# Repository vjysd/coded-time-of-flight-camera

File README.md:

# Coded Time of Flight Imaging System

## Motivation
Depth accuracy has always been an issue with range imaging technologies. Conventional continuous wave time of flight imaging technologies face multipath, scattering and reflection artifacts. Ultrafast imaging got fascinating ever since Doc Edgerton synchronized his electronic stroboscope with a special high-speed motion-picture-camera so that with each flash, exactly one frame of film was exposed. Visualizing and capturing action at speeds beyond human perception will help us in studying a lot of physical phenomenon like scattering, reflection, and interaction with matter. Here we propose a coded time of flight imaging technique to capture light in motion and to ameliorate depth accuuracy.

## Idea
To address the above mentioned issues, we constructed a coded time of flight camera using the PMD 19k-S3 sensor. This involved design of cyclone IV FPGA, soft core processor programming & optical system development. We carefully chose a broadband code instead of a continuous wave to modulate image sensor and light source. A detailed instrumental manual to build your own coded time of flight camera can be found at the end of this page.

## Approach
We exploited the concept of time resolved imaging to capture light in motion. A phase modulated light source locked with image sensor served this purpose. To address the issue of depth accuracy as our second intent, we constructed a mathematical model of multi-frequency light source de-multiplexing, wherein multiple light sources running at different frequencies were used to improve depth accuracy. A broadband signal, accommodating all the bins from multiple light sources was used to modulate the image sensor. This method proved to be more economical and efficient than current models where multiple cameras are used to serve the same purpose.

## HOW TO
Please use the diy_tof.pdf file to find all the necessary information about rebuilding the system from scratch.

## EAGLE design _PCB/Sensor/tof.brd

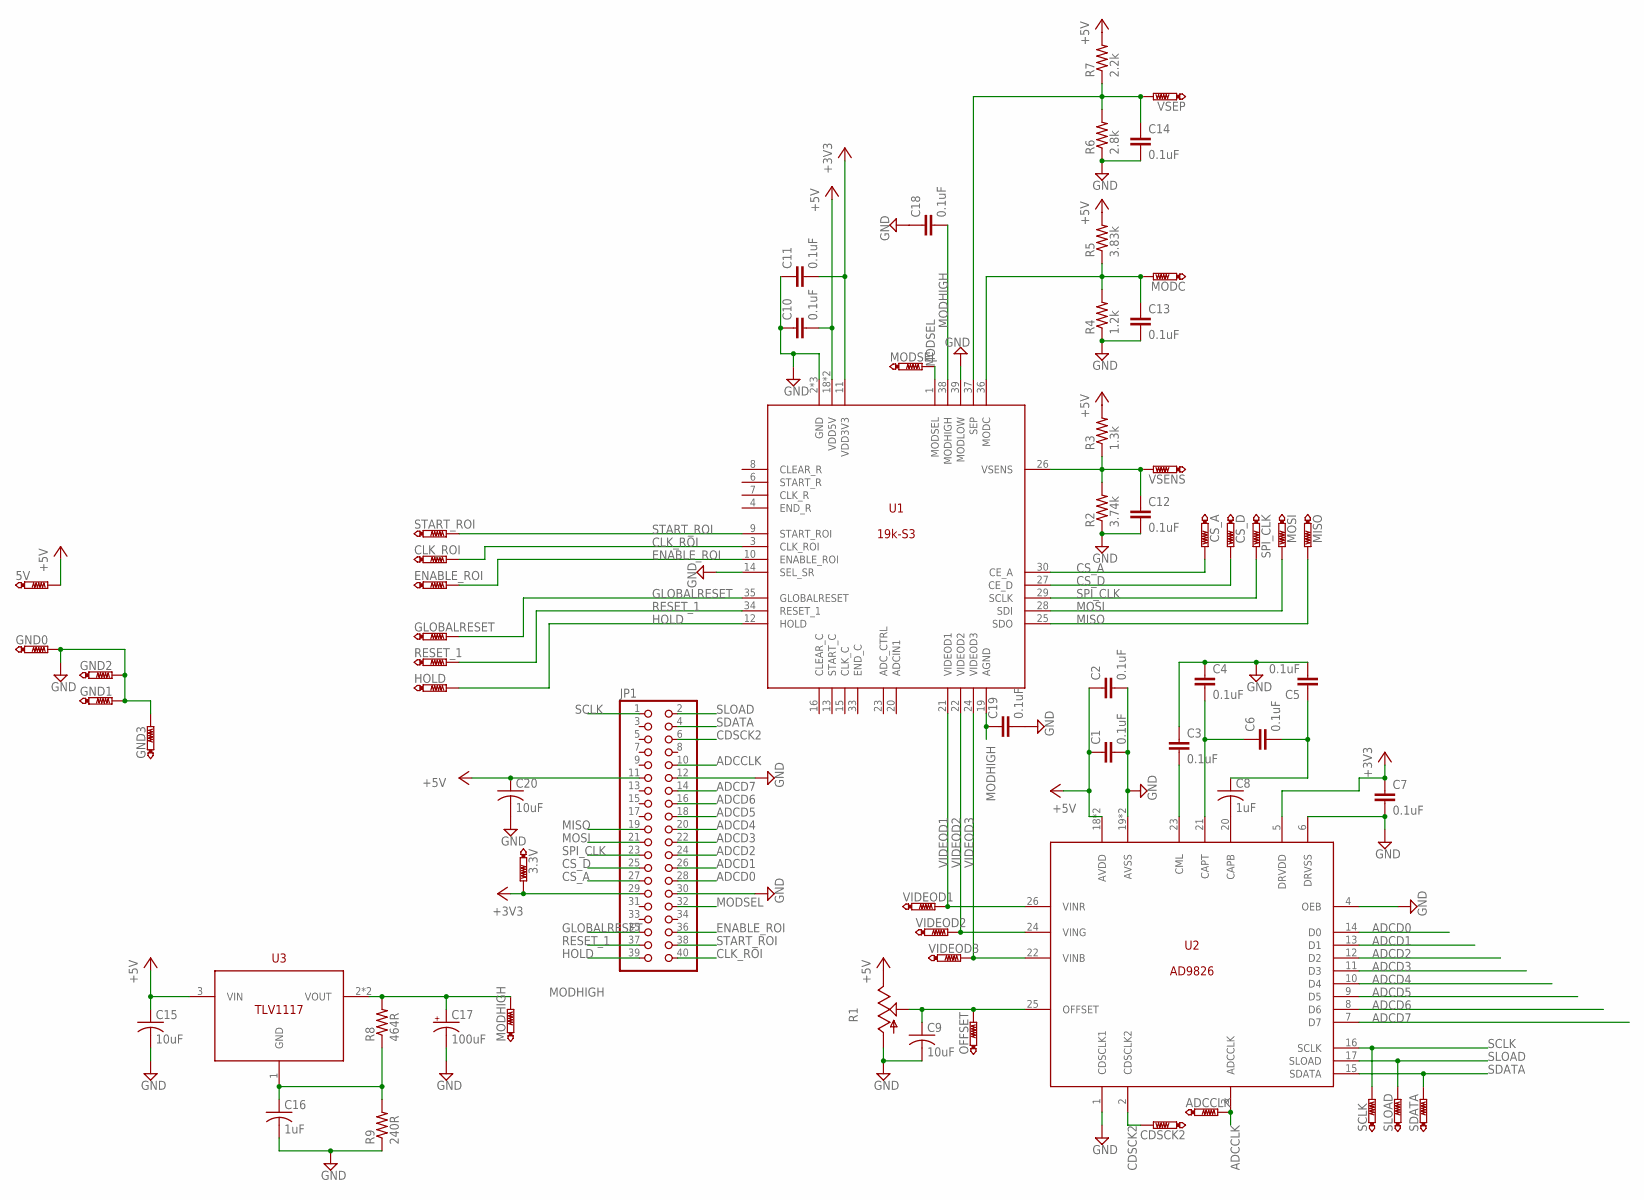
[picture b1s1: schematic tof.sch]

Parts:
3.3V, 5V: PTR1PAD1-13; P1-13
ADCCLK: PTR1PAD1-13; P1-13
C1, C2, C3, C4, C5, C6, C7, C10, C11, C12, C13, C14, C18, C19: 0.1uF; C0805
C8, C16: 1uF; C0805
C9, C15, C20: 10uF; C0805
C17: 100uF; PANASONIC_F
CDSCK2: PTR1PAD1-13; P1-13
CLK_ROI: PTR1PAD1-13; P1-13
CS_A: PTR1PAD1-13; P1-13
CS_D: PTR1PAD1-13; P1-13
ENABLE_ROI: PTR1PAD1-13; P1-13
GLOBALRESET: PTR1PAD1-13; P1-13
GND0, GND1, GND2, GND3: PTR1PAD1-13; P1-13
HOLD: PTR1PAD1-13; P1-13
JP1: PINHD-2X20; SMD-40
MISO: PTR1PAD1-13; P1-13
MODC: PTR1PAD1-13; P1-13
MODHIGH: PTR1PAD1-13; P1-13
MODSEL: PTR1PAD1-13; P1-13
MOSI: PTR1PAD1-13; P1-13
OFFSET: PTR1PAD1-13; P1-13
R1: TRIM_US-S63P; S63P
R2: 3.74k; R0805
R3: 1.3k; R0805
R4: 1.2k; R0805
R5: 3.83k; R0805
R6: 2.8k; R0805
R7: 2.2k; R0805
R8: 464R; R0805
R9: 240R; R0805
RESET_1: PTR1PAD1-13; P1-13
SCLK: PTR1PAD1-13; P1-13
SDATA: PTR1PAD1-13; P1-13
SLOAD: PTR1PAD1-13; P1-13
SPI_CLK: PTR1PAD1-13; P1-13
START_ROI: PTR1PAD1-13; P1-13
U1: 19K-S3; TLCC40
U2: AD9826; SSOP28
U3: TLV1117; SOT223
VIDEOD1, VIDEOD2, VIDEOD3: PTR1PAD1-13; P1-13
VSENS: PTR1PAD1-13; P1-13
VSEP: PTR1PAD1-13; P1-13

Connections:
+3V3: 3.3V.TP, C7.1, C11.2, JP1.29, U1.11 (VDD3V3), U2.5 (DRVDD)
+5V: 5V.TP, C1.1, C2.1, C10.2, C15.1, C20.1, JP1.11, R1.E, R3.2, R5.2, R7.2, U1.18 (VDD5V), U1.40 (VDD5V), U2.18 (AVDD), U2.28 (AVDD), U3.3 (VIN)
ADCCLK: ADCCLK.TP, JP1.10, U2.3 (ADCCLK)
ADCD0: JP1.28, U2.14 (D0)
ADCD1: JP1.26, U2.13 (D1)
ADCD2: JP1.24, U2.12 (D2)
ADCD3: JP1.22, U2.11 (D3)
ADCD4: JP1.20, U2.10 (D4)
ADCD5: JP1.18, U2.9 (D5)
ADCD6: JP1.16, U2.8 (D6)
ADCD7: JP1.14, U2.7 (D7)
CAPT: C4.2, C6.1, U2.21 (CAPT)
CDSCK2: CDSCK2.TP, JP1.6, U2.2 (CDSCLK2)
CLK_ROI: CLK_ROI.TP, JP1.40, U1.3 (CLK_ROI)
CML: C3.2, U2.23 (CML)
CS_A: CS_A.TP, JP1.27, U1.30 (CE_A)
CS_D: CS_D.TP, JP1.25, U1.27 (CE_D)
ENABLE_ROI: ENABLE_ROI.TP, JP1.36, U1.10 (ENABLE_ROI)
GLOBALRESET: GLOBALRESET.TP, JP1.35, U1.35 (GLOBALRESET)
GND: C1.2, C2.2, C3.1, C4.1, C5.2, C7.2, C9.2, C10.1, C11.1, C12.2, C13.2, C14.2, C15.2, C16.2, C17.-, C18.1, C19.2, C20.2, GND0.TP, GND1.TP, GND2.TP, GND3.TP, JP1.12, JP1.30, R1.A, R2.1, R4.1, R6.1, R9.1, U1.2 (GND), U1.5 (GND), U1.14 (SEL_SR), U1.39 (MODLOW), U1.PAD (GND), U2.1 (CDSCLK1), U2.4 (OEB), U2.6 (DRVSS), U2.19 (AVSS), U2.27 (AVSS)
HOLD: HOLD.TP, JP1.39, U1.12 (HOLD)
MISO: JP1.19, MISO.TP, U1.25 (SDO)
MODHIGH: C17.+, C18.2, C19.1, MODHIGH.TP, R8.2, U1.19 (AGND), U1.38 (MODHIGH), U3.2 (VOUT), U3.4 (VOUT)
MODSEL: JP1.32, MODSEL.TP, U1.1 (MODSEL)
MOSI: JP1.21, MOSI.TP, U1.28 (SDI)
unnamed: C9.1, OFFSET.TP, R1.S, U2.25 (OFFSET)
unnamed: C8.2, U2.20 (CAPB)
unnamed: C5.1, C6.2, C8.1
unnamed: C16.1, R8.1, R9.2, U3.1 (GND)
unnamed: C12.1, R2.2, R3.1, U1.26 (VSENS), VSENS.TP
unnamed: C13.1, MODC.TP, R4.2, R5.1, U1.36 (MODC)
unnamed: C14.1, R6.2, R7.1, U1.37 (SEP), VSEP.TP
RESET_1: JP1.37, RESET_1.TP, U1.34 (RESET_1)
SCLK: JP1.1, SCLK.TP, U2.16 (SCLK)
SDATA: JP1.4, SDATA.TP, U2.15 (SDATA)
SLOAD: JP1.2, SLOAD.TP, U2.17 (SLOAD)
SPI_CLK: JP1.23, SPI_CLK.TP, U1.29 (SCLK)
START_ROI: JP1.38, START_ROI.TP, U1.9 (START_ROI)
VIDEOD1: U1.21 (VIDEOD1), U2.26 (VINR), VIDEOD1.TP
VIDEOD2: U1.22 (VIDEOD2), U2.24 (VING), VIDEOD2.TP
VIDEOD3: U1.24 (VIDEOD3), U2.22 (VINB), VIDEOD3.TP

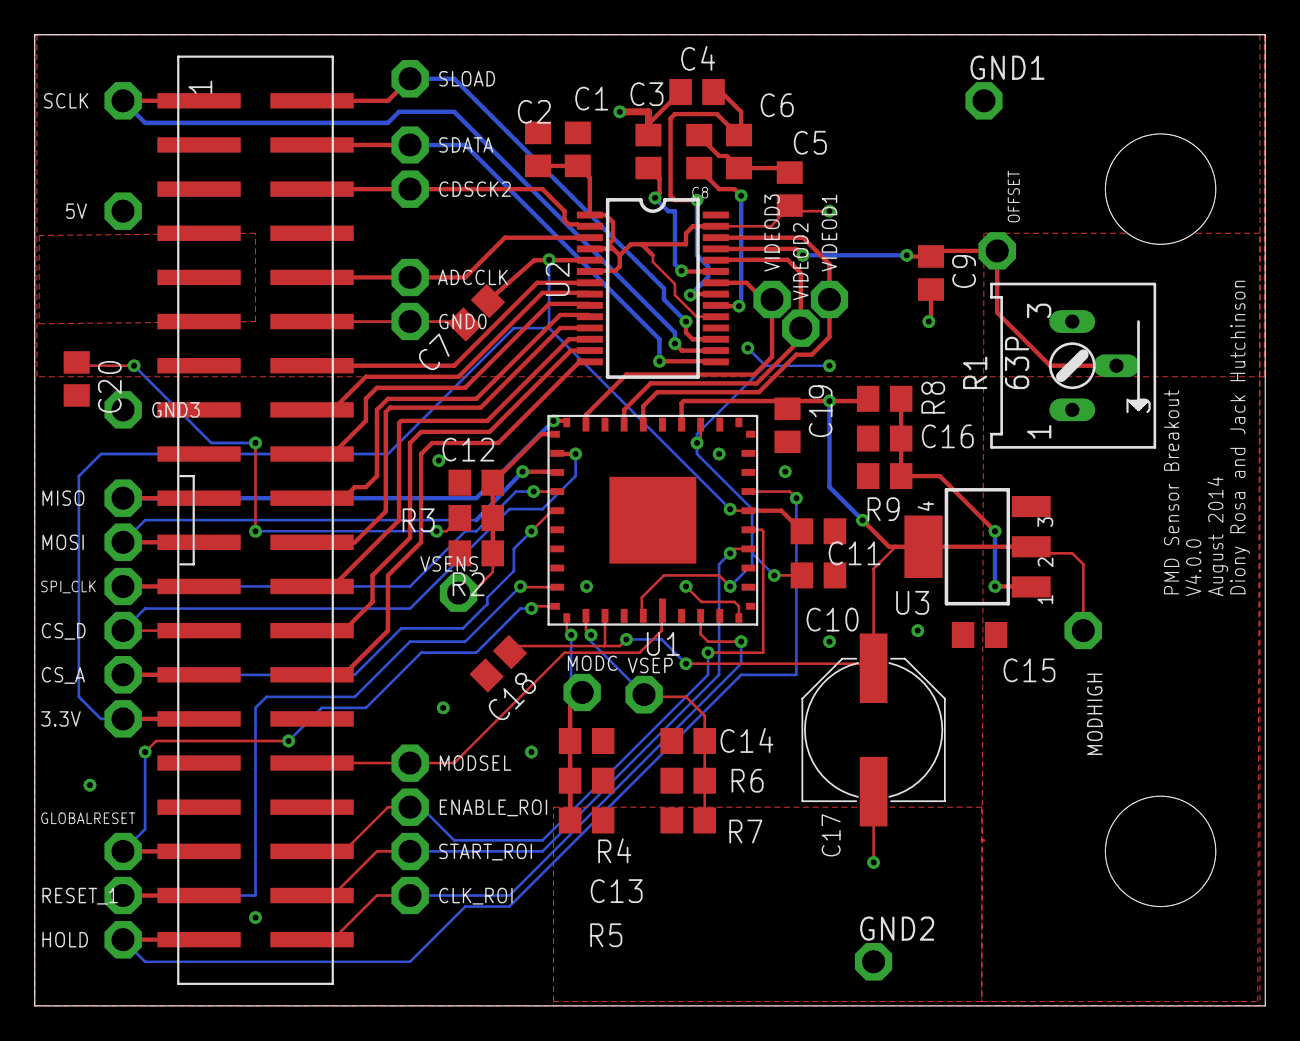
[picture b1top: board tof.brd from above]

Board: 2 copper layers, 70.8 x 55.9 mm, 64 parts (0 on the bottom side), 41 nets.

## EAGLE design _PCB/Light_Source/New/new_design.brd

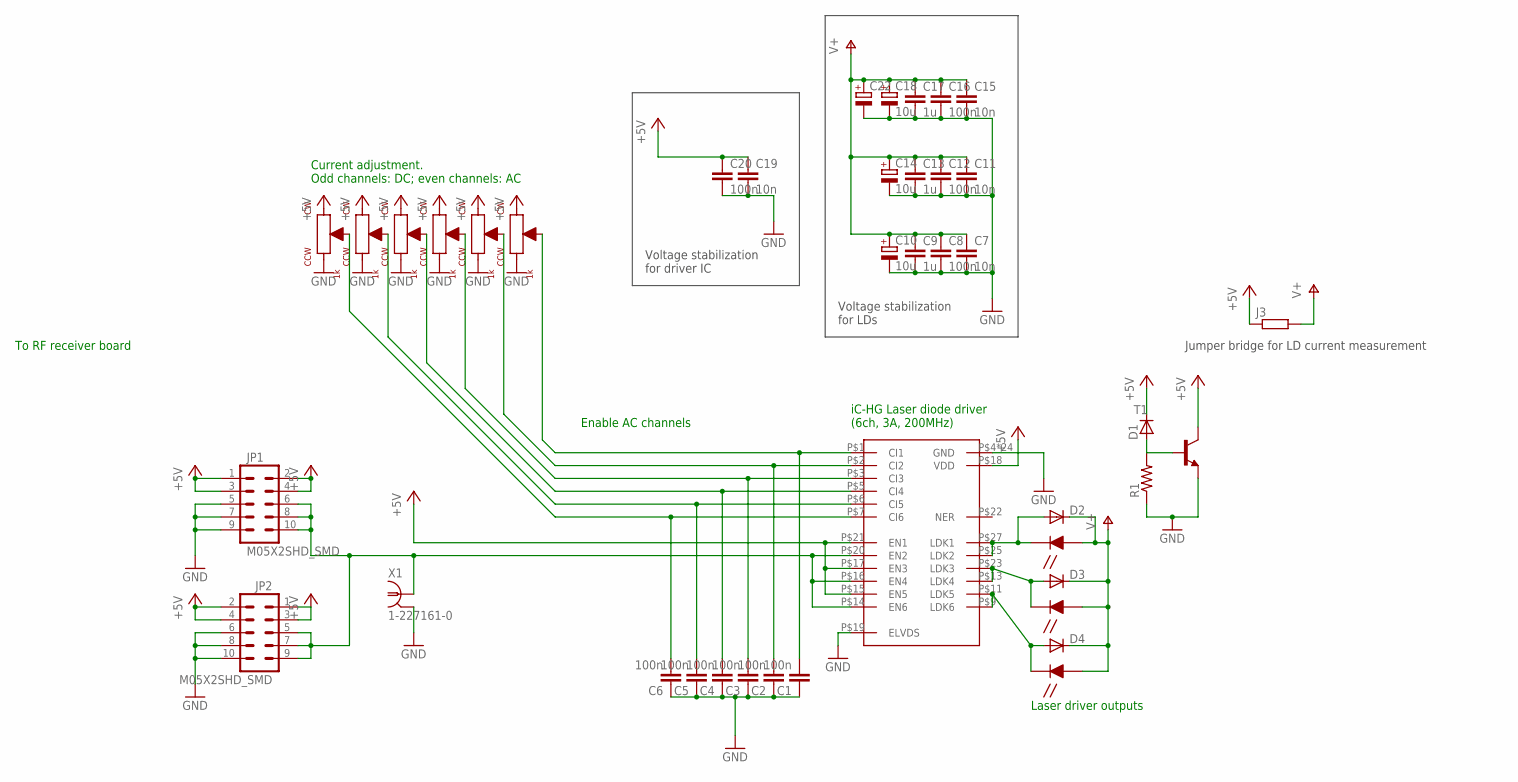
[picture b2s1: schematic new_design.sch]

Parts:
C1, C2, C3, C4, C5, C6, C8, C12, C16, C20: 100n; C0402K
C7, C11, C15, C19: 10n; C0402K
C9, C13, C17: 1u; C0603
C10, C14, C18: 10u; SMC_B
C22: CPOL-EUCT7343; CT7343
D1: D-SMB; SMB
D2, D3, D4: DIODE-SOD523; SOD523
IC1: IC-HGTHERMAL; QFN28-PAD
J3: R-EU_R1210; R1210
JP1, JP2: M05X2SHD_SMD; 2X5-SHROUDED_SMD
LD1, LD2, LD3: LASER; LD-FLAT
P1, P2, P3, P4, P5, P6: 1k; EVM-1D
R1: RESISTOR0805-RES; 0805
T1: -NPN-SOT223; SOT223
X1: 1-227161-0; AMP_227161

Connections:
+5V: C19.1, C20.1, D1.1 (C), IC1.P$15 (EN5), IC1.P$17 (EN3), IC1.P$18 (VDD), IC1.P$21 (EN1), J3.1, JP1.1, JP1.2, JP1.3, JP1.4, JP2.1, JP2.2, JP2.3, JP2.4, P1.CW, P2.CW, P3.CW, P4.CW, P5.CW, P6.CW, T1.4 (C)
AC_EN: IC1.P$14 (EN6), IC1.P$16 (EN4), IC1.P$20 (EN2), JP1.6, JP1.8, JP1.10, JP2.5, JP2.7, JP2.9, X1.1
GND: C1.1, C2.1, C3.1, C4.1, C5.1, C6.1, C7.2, C8.2, C9.2, C10.-, C11.2, C12.2, C13.2, C14.-, C15.2, C16.2, C17.2, C18.-, C19.2, C20.2, C22.-, IC1.P$4 (GND), IC1.P$8 (GND), IC1.P$10 (GND), IC1.P$12 (GND), IC1.P$19 (ELVDS), IC1.P$24 (GND), IC1.P$26 (GND), IC1.P$28 (GND), IC1.P$29 (GND), IC1.P$30 (GND), IC1.P$31 (GND), IC1.P$32 (GND), IC1.P$33 (GND), IC1.P$34 (GND), IC1.P$35 (GND), IC1.P$36 (GND), IC1.P$37 (GND), IC1.P$38 (GND), IC1.P$39 (GND), IC1.P$40 (GND), IC1.P$41 (GND), IC1.P$42 (GND), IC1.P$43 (GND), IC1.P$44 (GND), IC1.P$45 (GND), JP1.5, JP1.7, JP1.9, JP2.6, JP2.8, JP2.10, P1.CCW, P2.CCW, P3.CCW, P4.CCW, P5.CCW, P6.CCW, R1.1, T1.3 (E), X1.2
unnamed: C2.2, IC1.P$2 (CI2), P2.W
unnamed: C4.2, IC1.P$5 (CI4), P4.W
unnamed: C6.2, IC1.P$7 (CI6), P6.W
unnamed: C1.2, IC1.P$1 (CI1), P1.W
unnamed: C3.2, IC1.P$3 (CI3), P3.W
unnamed: C5.2, IC1.P$6 (CI5), P5.W
unnamed: D4.A, IC1.P$9 (LDK6), IC1.P$11 (LDK5), LD3.C
unnamed: D3.A, IC1.P$13 (LDK4), IC1.P$23 (LDK3), LD2.C
unnamed: D2.A, IC1.P$25 (LDK2), IC1.P$27 (LDK1), LD1.C
unnamed: D1.2 (A), R1.2, T1.1 (B)
V+: C7.1, C8.1, C9.1, C10.+, C11.1, C12.1, C13.1, C14.+, C15.1, C16.1, C17.1, C18.+, C22.+, D2.C, D3.C, D4.C, J3.2, LD1.A, LD2.A, LD3.A

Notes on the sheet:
To RF receiver board
Current adjustment. Odd channels: DC; even channels: AC
Enable AC channels
iC-HG Laser diode driver (6ch, 3A, 200MHz)
Laser driver outputs
Voltage stabilization for LDs
Voltage stabilization for driver IC
Jumper bridge for LD current measurement

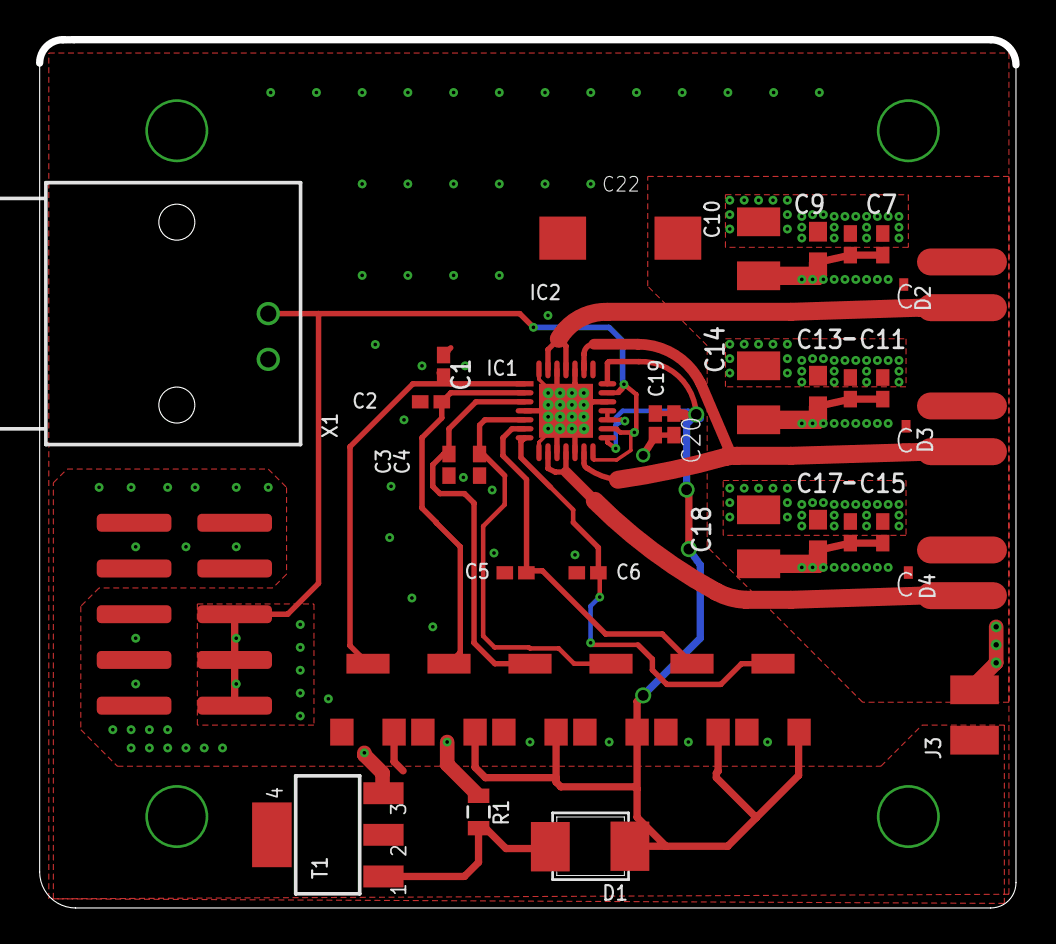
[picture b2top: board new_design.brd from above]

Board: 4 copper layers, 54.2 x 48.0 mm, 41 parts (1 on the bottom side), 14 nets.

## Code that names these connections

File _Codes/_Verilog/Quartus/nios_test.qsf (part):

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set_global_assignment -name PARTITION_COLOR 16764057 -entity test -section_id Top
set_instance_assignment -name PARTITION_HIERARCHY root_partition -to | -entity test -section_id Top
set_location_assignment PIN_AB22 -to SCLK
set_location_assignment PIN_AC15 -to SLOAD
set_location_assignment PIN_Y17 -to SDATA
set_location_assignment PIN_Y16 -to CDSCLK2
set_location_assignment PIN_AE16 -to CDSCLK1
set_location_assignment PIN_AE15 -to ADCCLK
set_location_assignment PIN_AF16 -to DATA[7]
set_location_assignment PIN_AF15 -to DATA[6]
set_location_assignment PIN_AE21 -to DATA[5]
set_location_assignment PIN_AH25 -to CS_A
set_location_assignment PIN_AC22 -to DATA[4]
set_location_assignment PIN_AG25 -to CS_D
set_location_assignment PIN_AF21 -to DATA[3]
set_location_assignment PIN_AF22 -to SPI_CLK
set_location_assignment PIN_AD22 -to DATA[2]
set_location_assignment PIN_AE22 -to MOSI
set_location_assignment PIN_AD25 -to DATA[1]
set_location_assignment PIN_AF25 -to MISO
set_location_assignment PIN_AE25 -to DATA[0]
set_location_assignment PIN_AE24 -to MODSEL
set_location_assignment PIN_AH26 -to START_ROI
set_location_assignment PIN_AH23 -to HOLD
set_location_assignment PIN_AG26 -to CLK_ROI
set_location_assignment PIN_AF20 -to RESET_1
set_location_assignment PIN_AG23 -to ENABLE_ROI
set_location_assignment PIN_AE20 -to GLOBALRESET
set_location_assignment PIN_AF26 -to SEL_SR
set_instance_assignment -name PARTITION_HIERARCHY root_partition -to | -entity PMD -section_id Top
set_global_assignment -name SEARCH_PATH altera/12.0sp2/quartus/libraries/vhdl/ieee/ -tag from_archive
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
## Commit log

2016-02-24 Added README
2016-02-24 All codes added
2016-02-24 Added diytof.pdf

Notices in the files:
_Codes/_Verilog/Quartus/nios_test.qsf:
Copyright (C) 1991-2012 Altera Corporation
parts and their libraries:
SparkFun-Connectors_2: Licensing: Creative Commons ShareAlike 4.0 International - https://creativecommons.org/licenses/by-sa/4.0
